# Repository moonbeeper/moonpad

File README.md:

# moonpad

> [!NOTE]
> This project is still not in a finished state. It does not work.
> This project comes from [Highway To Undercity](https://highway.hackclub.com/projects/moonbeeper/moonpad)

It's a modular macropad. Simple as that. You have an oled screen in the macropad and 2 modules that can be daisy chained and hot swapped. These two modules are the knobs and sliders module as I didn't want to overcomplicate my first project.

The primary reason for making this project was to just learn how to make PCBs and use microcontrollers like the RP2040 and ATTINY. It was a great adventure and I think I learned a lot. I mean, there's sure a lot of room for improvement but I'm happy with the result.

## Images

> Macropad

> Knobs Module

> Sliders Module

> Macropad PCB

> Knobs Module PCB

> Sliders Module PCB

## BOM

> **NOTE:** This is a copy of the BOM.csv file. The shipping cost might be actually higher than the price listed here.

| Item | Quantity | LCSC Part Number | Cost EUR | Cost USD | Link |
|---|---|---|---|---|---|
| 1uF Ceramic Cap | 34 | C116352 | 0,49 € | $0,56 | <https://lcsc.com/product-detail/Multilayer-Ceramic-Capacitors-MLCC-SMD-SMT_Samsung-Electro-Mechanics-CL21B105KAFNNNE_C116352.html> |
| 4.7k Ohm Resistor | 16 | C60816 | 0,20 € | $0,22 | <https://lcsc.com/product-detail/Chip-Resistor-Surface-Mount_YAGEO-RC0805FR-074K7L_C60816.html> |
| 10k Ohm Resistor | 8 | C17414 | 0,16 € | $0,18 | <https://lcsc.com/product-detail/Chip-Resistor-Surface-Mount_UNI-ROYAL-Uniroyal-Elec-0805W8F1002T5E_C17414.html> |
| 1N4148 Diode | 19 | C68883 | 0,55 € | $0,63 | <https://lcsc.com/product-detail/Switching-Diodes_Vishay-Intertech-LL4148-GS08_C68883.html> |
| TCA9546APWR | 1 | C201653 | 0,63 € | $0,73 | <https://lcsc.com/product-detail/Signal-Switches-Multiplexers-Decoders_TI-TCA9546APWR_C201653.html> |
| Cherry MX Red Switch | 8 | --- | 5,72 € | $6,68 | <https://es.aliexpress.com/item/1005006255961111.html> |
| XIAO RP2040 | 1 | --- | 6,25 € | $7,30 | <https://es.aliexpress.com/item/1005004459618789.html> |
| Oled Display 128x32 | 1 | --- | 1,97 € | $2,30 | <https://es.aliexpress.com/item/1005008640132638.html> |
| 5 pin magentic connector | 11 | --- | 3,13 € | $3,66 | <https://es.aliexpress.com/item/1005006531774076.html> |
| TS5A23166DCUR | 8 | C49148 | 3,85 € | $4,42 | <https://lcsc.com/product-detail/Analog-Switches-Multiplexers_Texas-Instruments-TS5A23166DCUR_C49148.html> |
| ATTINY1616-SNR | 2 | C609652 | 2,69 € | $3,09 | <https://lcsc.com/product-detail/Microcontrollers-MCU-MPU-SOC_Microchip-Tech-ATTINY1616-SNR_C609652.html> |
| TMUX4052PWR (Q1) | 2 | C20345958 | 0,59 € | $0,68 | <https://lcsc.com/product-detail/Analog-Switches-Multiplexers_TI-TMUX4052PWRQ1_C20345958.html> |
| ATTINY414-SSF | 2 | C1338163 | 2,73 € | $3,13 | <https://lcsc.com/product-detail/Microcontrollers-MCU-MPU-SOC_Microchip-Tech-ATTINY414-SSF_C1338163.html> |
| TCA4311ADGKR | 2 | C130025 | 1,81 € | $2,08 | <https://lcsc.com/product-detail/Signal-Buffers-Repeaters-Splitters_TI-TCA4311ADGKR_C130025.html> |
| Vertical SPDT Switch | 2 | C3008584 | 0,39 € | $0,44 | <https://lcsc.com/product-detail/Slide-Switches_SHOU-HAN-MSS12C02LS-HB2-0_C3008584.html> |
| ALPSALPINE RS45111A900F Potentiometer | 2 | C470640 | 2,81 € | $3,24 | <https://lcsc.com/product-detail/Potentiometers-Variable-Resistors_ALPSALPINE-RS45111A900F_C470640.html> |
| PMOSFET | 2 | C15127 | 0,56 € | $0,64 | <https://lcsc.com/product-detail/MOSFETs_Alpha-Omega-Semicon-AO3401A_C15127.html> |
| Header Pins | 2 | --- | 0,99 € | $1,16 | <https://es.aliexpress.com/item/4000873858801.html> |
| Encoder ALPSALPINE EC11E18244AU | 3 | C202365 | 5,13 € | $5,89 | <https://lcsc.com/product-detail/Rotary-Encoders_ALPSALPINE-EC11E18244AU_C202365.html> |
| JLCPCB Macropad PCB | 5 | --- | 3,32 € | $4,00 | --- |
| JLCPCB Slider PCB | 5 | --- | 5,98 € | $7,00 | --- |
| JLCPCB Knobs PCB | 5 | --- | 5,98 € | $7,00 | --- |
| M2 Heat Inserts OD3.5 Length 4mm | 12 | --- | 2,14 € | $2,50 | <https://es.aliexpress.com/item/1005003582355741.html> |
| M2 Allen Bolts 14mm Stainless Steel | 4 | --- | 2,03 € | $2,37 | <https://es.aliexpress.com/item/32810872544.html> |
| M2 Allen Bolts 10mm Stainless Steel | 8 | --- | 1,77 € | $2,07 | <https://es.aliexpress.com/item/32810872544.html> |
| Cherry MX Plate mounted Stabilizer | 1 | --- | 5,44 € | $6,35 | <https://es.aliexpress.com/item/1005001831944910.html> |
| 1U DSA Yellow Keycaps | 7 | --- | 3,39 € | $3,96 | <https://es.aliexpress.com/item/1005002906017844.html> |
| 2U DSA Gray Keycaps | 1 | --- | 6,92 € | $8,08 | <https://es.aliexpress.com/item/4001241957677.html> |
| UPDI Friend (Programmer) | 1 | --- | 7,77 € | $9,08 | <https://es.aliexpress.com/item/1005007180681621.html> |
| Flux | 1 | --- | 3,63 € | $4,24 | <https://es.aliexpress.com/item/1005006982454206.html> |
| ~Shipping | --- | --- | 15,07 € | $17,60 | --- |
| TOTAL | --- | --- | 104,09 € | $121,28 | --- |
|  |  |  |  |  |  |

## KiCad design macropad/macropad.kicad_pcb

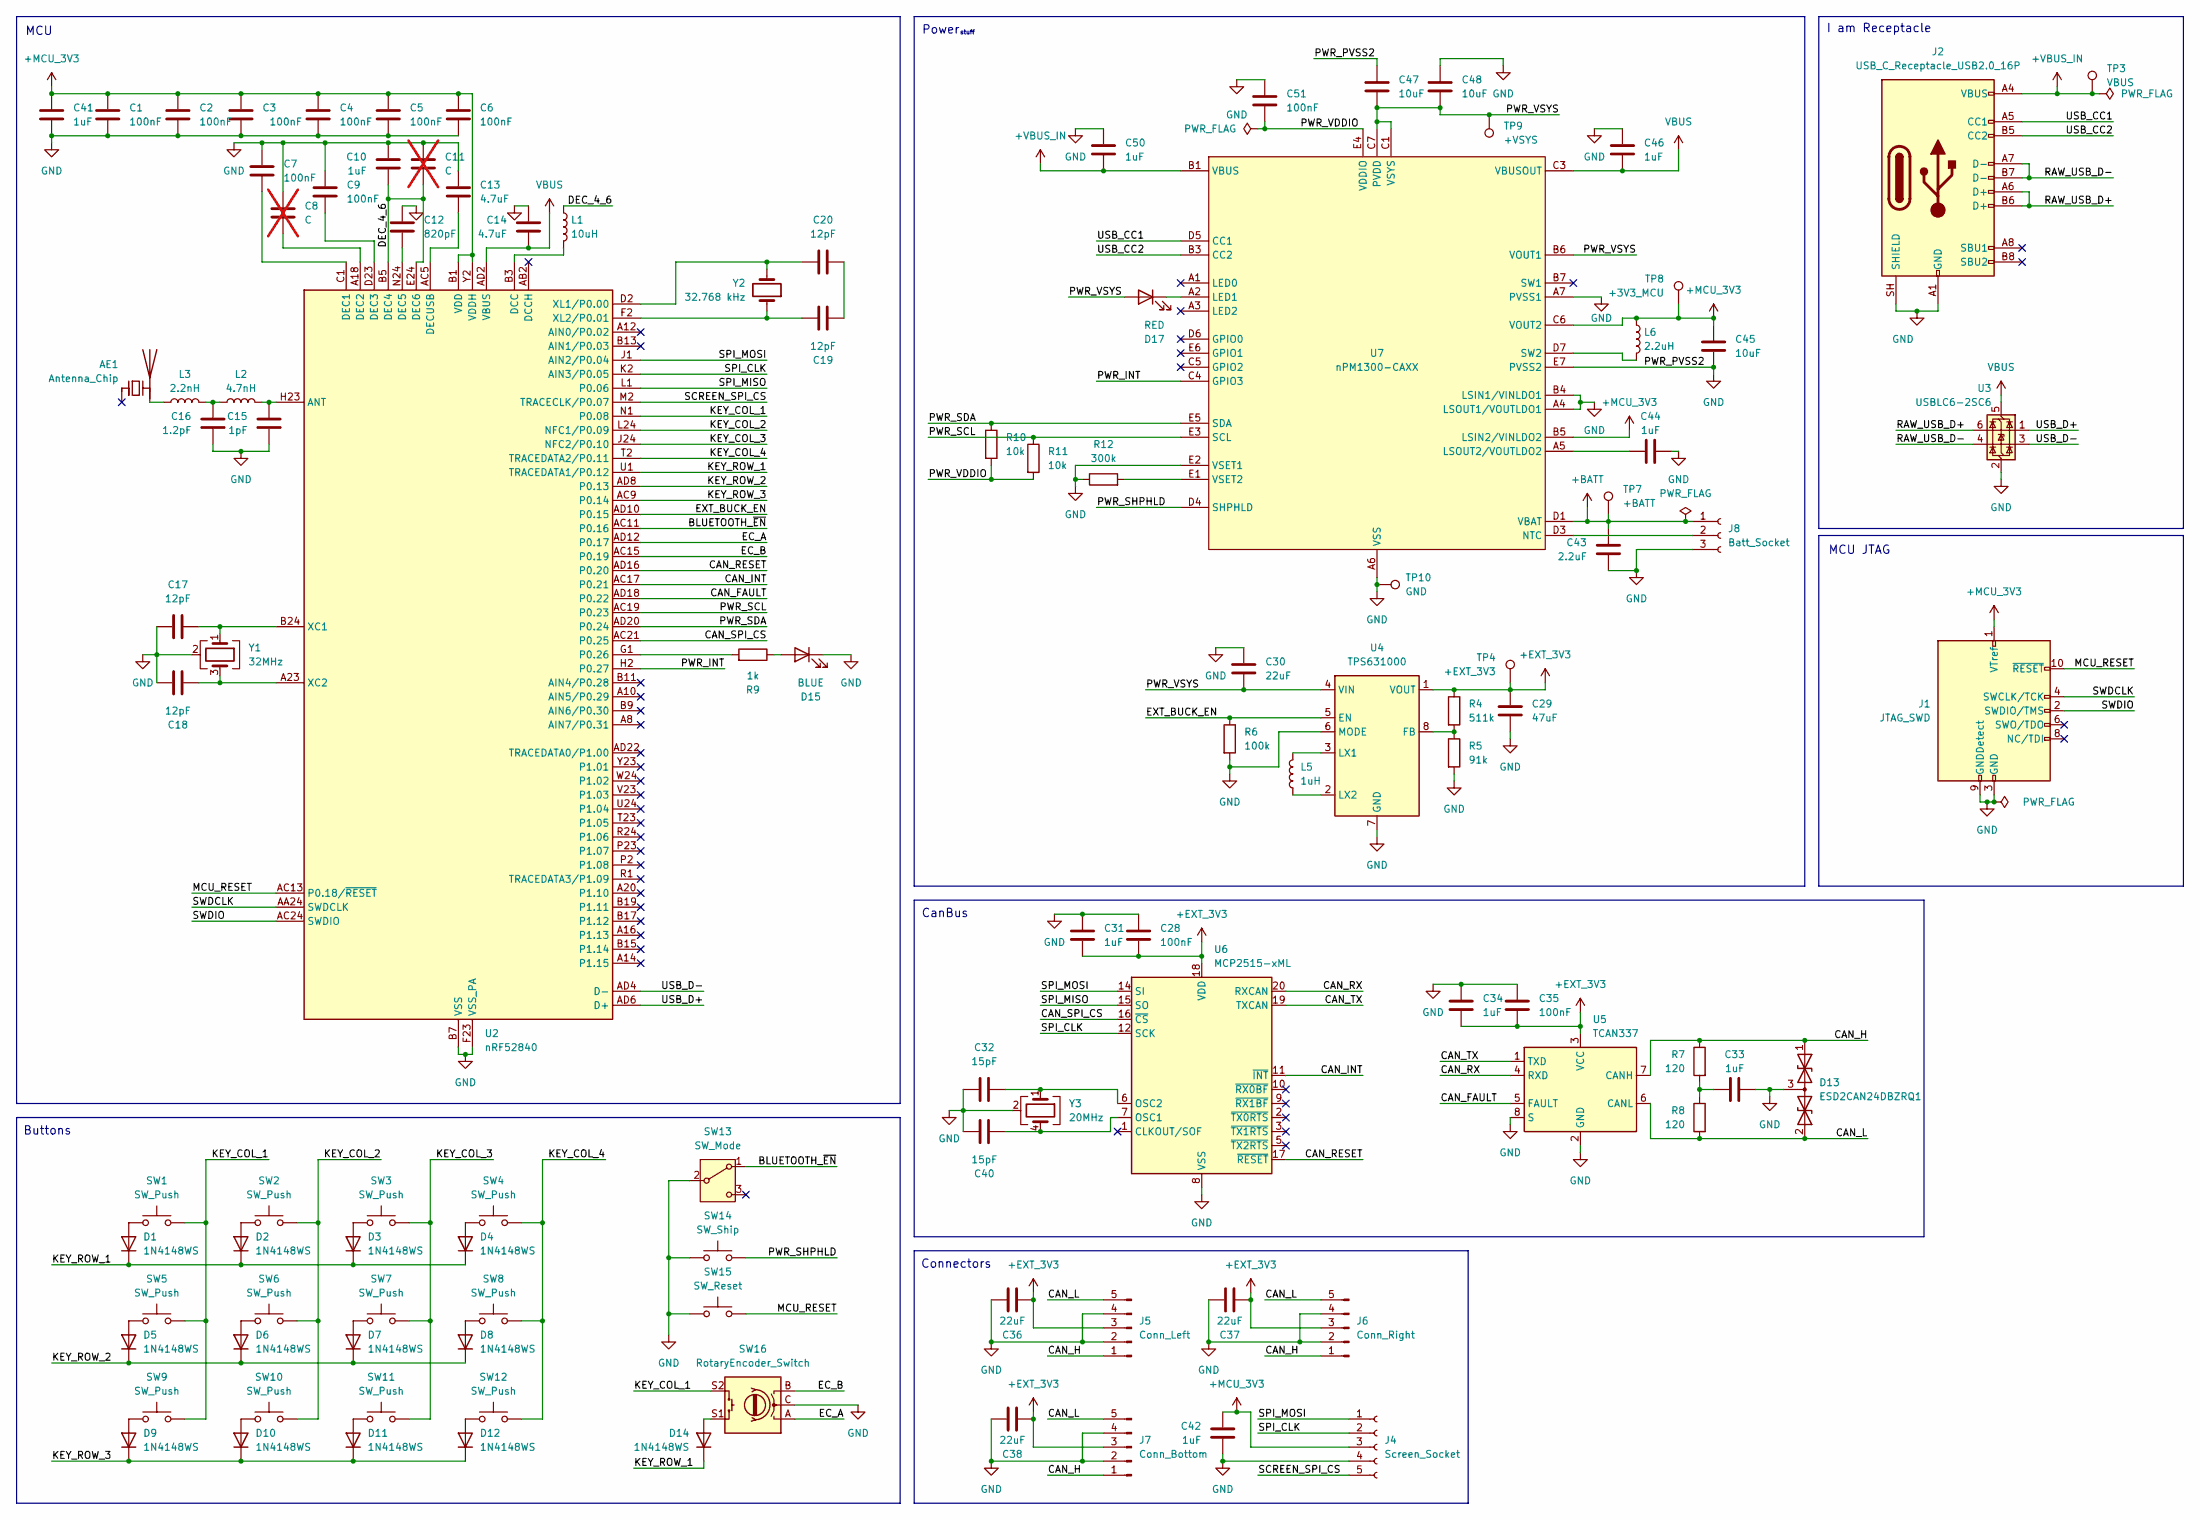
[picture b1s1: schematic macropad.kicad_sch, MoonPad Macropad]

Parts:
AE1: Antenna_Chip; D_1206_3216Metric; MPN ANT3216LL00R2400A; LCSC C293767
C1, C2, C3, C4, C5, C6, C7, C9, C28, C35, C51: 100nF; C_0603_1608Metric; MPN CC0603KRX7R9BB104; LCSC C14663
C8, C11: C; not fitted
C10, C31, C33, C34, C41, C42, C44, C46, C50: 1uF; C_0603_1608Metric; MPN CL10B105KB8NQNC; LCSC C5199872
C12: 820pF; C_0603_1608Metric; MPN CC0603JRNPO9BN821; LCSC C107057
C13, C14: 4.7uF; C_0603_1608Metric; MPN GRM188Z71C475KE21D; LCSC C389010
C15: 1pF; C_0402_1005Metric; MPN CC0402BRNPO9BN1R0; LCSC C309455
C16: 1.2pF; C_0402_1005Metric; MPN CC0402BRNPO9BN1R2; LCSC C327292
C17, C18, C19, C20: 12pF; C_0603_1608Metric; MPN CC0603GRNPO9BN120; LCSC C519450
C29: 47uF; C_0805_2012Metric; MPN GRM21BR61A476ME15L; LCSC C124129
C30, C36, C37, C38: 22uF; C_0805_2012Metric; MPN CL21A226MPQNNNE; LCSC C29277
C32, C40: 15pF; C_0603_1608Metric; MPN CC0603GRNPO9BN150; LCSC C519451
C43: 2.2uF; C_0603_1608Metric; MPN CL10A225KB8NNNC; LCSC C913904
C45, C47, C48: 10uF; C_0603_1608Metric; MPN GRM188R61E106KA73D; LCSC C344022
D1, D2, D3, D4, D5, D6, D7, D8, D9, D10, D11, D12, D14: 1N4148WS; D_SOD-323; MPN 1N4148WS; LCSC C917117
D13: ESD2CAN24DBZRQ1; SOT-23-3; MPN ESD2CAN24DBZRQ1
D15: BLUE; LED_0603_1608Metric; MPN GL0603UB01; LCSC C51933294
D17: RED; LED_0603_1608Metric; MPN GL0603UR01; LCSC C51933292
J1: JTAG_SWD; PinHeader_2x05_P1.27mm_Vertical
J2: USB_C_Receptacle_USB2.0_16P; USB_C_Receptacle_G-Switch_GT-USB-7010ASV; MPN GT-USB-7010ASV; LCSC C2988369
J4: Screen_Socket; PinHeader_1x05_P2.00mm_Vertical
J5: Conn_Left; PinHeader_1x05_P2.00mm_Vertical
J6: Conn_Right; PinHeader_1x05_P2.00mm_Vertical
J7: Conn_Bottom; PinHeader_1x05_P2.00mm_Vertical
J8: Batt_Socket; PinHeader_1x05_P2.00mm_Vertical
L1: 10uH; L_0603_1608Metric; MPN MLZ1608N100LT000; LCSC C194437
L2: 4.7nH; L_0402_1005Metric; MPN LQG15HS4N7S02D; LCSC C86065
L3: 2.2nH; L_0402_1005Metric; MPN LQG15HS2N2S02D; LCSC C86061
L5: 1uH; L_1008_2520Metric; MPN DFE252012P-1R0M=P2; LCSC C882955
L6: 2.2uH; L_0805_2012Metric; MPN DFE201210U-2R2M=P2; LCSC C2049745
R4: 511k; R_0603_1608Metric; MPN FRC0603F5113TS; LCSC C2930114
R5: 91k; R_0603_1608Metric; MPN FRC0603F9102TS; LCSC C2907077
R6: 100k; R_0603_1608Metric; MPN FRC0603F1003TS; LCSC C2906980
R7, R8: 120; R_0603_1608Metric; MPN FRC0603F1200TS; LCSC C2906988
R9: 1k; R_0603_1608Metric; MPN FRC0603F1001TS; LCSC C2907002
R10, R11: 10k; R_0603_1608Metric; MPN FRC0603J103 TS; LCSC C2930027
R12: 300k; R_0603_1608Metric; MPN FRC0603F3003TS; LCSC C2930091
SW1, SW2, SW3, SW4, SW5, SW6, SW7, SW8, SW9, SW10, SW11, SW12: SW_Push; SW_Hotswap_Kailh_Choc_V1V2_1.00u
SW13: SW_Mode; SW-SMD_MK-12C02-G020; MPN MK-12C02-G020; LCSC C963206
SW14: SW_Ship; KEY-SMD_SKRTLAE010; MPN SKRTLAE010; LCSC C110293
SW15: SW_Reset; KEY-SMD_B3U-1000PM; MPN B3U-1000P; LCSC C231329
SW16: RotaryEncoder_Switch; RotaryEncoder_Alps_EC11E-Switch_Vertical_H20mm; MPN EC11E09244BS; LCSC C470742
TP3: VBUS; TestPoint_Pad_D1.5mm
TP4: +EXT_3V3; TestPoint_Pad_D1.5mm
TP7: +BATT; TestPoint_Pad_D1.5mm
TP8: +3V3_MCU; TestPoint_Pad_D1.5mm
TP9: +VSYS; TestPoint_Pad_D1.5mm
TP10: GND; TestPoint_Pad_D1.5mm
U2: nRF52840; Nordic_AQFN-73-1EP_7x7mm_P0.5mm; MPN NRF52840-QIAA-F-R7
U3: USBLC6-2SC6; SOT-23-6; MPN USBLC6-2SC6; LCSC C2827654
U4: TPS631000; SOT-583-8; MPN TPS631000DRLR; LCSC C5219190
U5: TCAN337; SOIC-8_3.9x4.9mm_P1.27mm; MPN TCAN337DR; LCSC C2860648
U6: MCP2515-xML; QFN-20-1EP_4x4mm_P0.5mm_EP2.7x2.7mm; MPN MCP2515T-I/ML; LCSC C96140
U7: nPM1300-CAXX; BGA-35_7x5_3.077x2.3775mm; MPN NPM1300-CAAA-R
Y1: 32MHz; Crystal_SMD_2016-4Pin_2.0x1.6mm; MPN TX201632M4BBCE2T; LCSC C5339095
Y2: 32.768 kHz; Crystal_SMD_2012-2Pin_2.0x1.2mm; MPN SC-20S,32.768kHz,20PPM,9pF; LCSC C97603
Y3: 20MHz; Crystal_SMD_3225-4Pin_3.2x2.5mm; MPN 2.1.3.1600011; LCSC C42420972

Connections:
+BATT: C43.1, J8.1, TP7.1 (1_1), U7.D1 (VBAT), U7.D2 (VBAT)
+EXT_3V3: C28.2, C29.1, C31.2, C34.2, C35.2, C36.1, C37.1, C38.1, J5.3, J6.3, J7.3, R4.1, TP4.1 (1_1), U4.1 (VOUT), U5.3 (VCC), U6.18 (VDD)
+MCU_3V3: C1.1, C2.1, C3.1, C4.1, C5.1, C6.1, C41.1, C42.1, C45.1, J1.1 (VTref), J4.3, L6.1, TP8.1 (1_1), U2.A22 (VDD), U2.AD14 (VDD), U2.AD23 (VDD), U2.B1 (VDD), U2.W1 (VDD), U2.Y2 (VDDH), U7.B5 (LSIN2/VINLDO2), U7.C6 (VOUT2)
+VBUS_IN: C50.2, J2.A4 (VBUS), J2.A9 (VBUS), J2.B4 (VBUS), J2.B9 (VBUS), TP3.1 (1_1), U7.B1 (VBUS), U7.B2 (VBUS)
/BLUETOOTH_~EN: SW13.1 (A), U2.AC11 (P0.16)
/CAN_FAULT: U2.AD18 (P0.22), U5.5 (FAULT)
/CAN_H: D13.1 (A1), J5.1, J6.1, J7.1, R7.1, U5.7 (CANH)
/CAN_INT: U2.AC17 (P0.21), U6.11 (~INT)
/CAN_L: D13.2 (A2), J5.5, J6.5, J7.5, R8.2, U5.6 (CANL)
/CAN_RESET: U2.AD16 (P0.20), U6.17 (~RESET)
/CAN_RX: U5.4 (RXD), U6.20 (RXCAN)
/CAN_SPI_CS: U2.AC21 (P0.25), U6.16 (~CS)
/CAN_TX: U5.1 (TXD), U6.19 (TXCAN)
/DEC_4_6: C10.2, C11.2, L1.1, U2.B5 (DEC4), U2.E24 (DEC6)
/EC_A: SW16.A, U2.AD12 (P0.17)
/EC_B: SW16.B, U2.AC15 (P0.19)
/EXT_BUCK_EN: R6.1, U2.AD10 (P0.15), U4.5 (EN)
/KEY_COL_1: SW1.2, SW5.2, SW9.2, SW16.S2, U2.N1 (P0.08)
/KEY_COL_2: SW2.2, SW6.2, SW10.2, U2.L24 (NFC1/P0.09)
/KEY_COL_3: SW3.2, SW7.2, SW11.2, U2.J24 (NFC2/P0.10)
/KEY_COL_4: SW4.2, SW8.2, SW12.2, U2.T2 (TRACEDATA2/P0.11)
/KEY_ROW_1: D1.1 (K), D2.1 (K), D3.1 (K), D4.1 (K), D14.1 (K), U2.U1 (TRACEDATA1/P0.12)
/KEY_ROW_2: D5.1 (K), D6.1 (K), D7.1 (K), D8.1 (K), U2.AD8 (P0.13)
/KEY_ROW_3: D9.1 (K), D10.1 (K), D11.1 (K), D12.1 (K), U2.AC9 (P0.14)
/MCU_RESET: J1.10 (~RESET), SW15.2, U2.AC13 (P0.18/~RESET)
/PWR_INT: U2.H2 (P0.27), U7.C4 (GPIO3)
/PWR_SCL: R11.1, U2.AC19 (P0.23), U7.E3 (SCL)
/PWR_SDA: R10.1, U2.AD20 (P0.24), U7.E5 (SDA)
/PWR_SHPHLD: SW14.2, U7.D4 (SHPHLD)
/PWR_VDDIO: C51.2, R10.2, R11.2, U7.E4 (VDDIO)
/PWR_VSYS: C30.2, C47.2, C48.2, D17.2 (A), TP9.1 (1_1), U4.4 (VIN), U7.B6 (VOUT1), U7.C1 (VSYS), U7.C2 (VSYS), U7.C7 (PVDD)
/RAW_USB_D+: J2.A6 (D+), J2.B6 (D+), U3.6 (I/O1)
/RAW_USB_D-: J2.A7 (D-), J2.B7 (D-), U3.4 (I/O2)
/SCREEN_SPI_CS: J4.5, U2.M2 (TRACECLK/P0.07)
/SPI_CLK: J4.2, U2.K2 (AIN3/P0.05), U6.12 (SCK)
/SPI_MISO: U2.L1 (P0.06), U6.15 (SO)
/SPI_MOSI: J4.1, U2.J1 (AIN2/P0.04), U6.14 (SI)
/SWDCLK: J1.4 (SWCLK/TCK), U2.AA24 (SWDCLK)
/SWDIO: J1.2 (SWDIO/TMS), U2.AC24 (SWDIO)
/USB_CC1: J2.A5 (CC1), U7.D5 (CC1)
/USB_CC2: J2.B5 (CC2), U7.B3 (CC2)
/USB_D+: U2.AD6 (D+), U3.1 (I/O1)
/USB_D-: U2.AD4 (D-), U3.3 (I/O2)
GND: C1.2, C2.2, C3.2, C4.2, C5.2, C6.2, C7.1, C8.1, C9.1, C10.1, C11.1, C12.1, C13.1, C14.1, C15.2, C16.2, C17.2, C18.2, C28.1, C29.2, C30.1, C31.1, C32.1, C33.2, C34.1, C35.1, C36.2, C37.2, C38.2, C40.1, C41.2, C42.2, C43.2, C44.2, C45.2, C46.1, C47.1, C48.1, C50.1, C51.1, D13.3 (common), D15.1 (K), J1.3 (GND), J1.5 (GND), J1.9 (GNDDetect), J2.A1 (GND), J2.A12 (GND), J2.B1 (GND), J2.B12 (GND), J2.SH (SHIELD), J4.4, J5.2, J5.4, J6.2, J6.4, J7.2, J7.4, J8.3, R5.2, R6.2, R12.1, SW13.2 (B), SW14.1, SW15.1, SW16.C, TP10.1 (1_1), U2.B7 (VSS), U2.EP (VSS), U2.F23 (VSS_PA), U3.2 (GND), U4.6 (MODE), U4.7 (GND), U5.2 (GND), U5.8 (S), U6.8 (VSS), U6.21 (EP), U7.A4 (LSOUT1/VOUTLDO1), U7.A6 (VSS), U7.A7 (PVSS1), U7.B4 (LSIN1/VINLDO1), U7.E2 (VSET1), U7.E7 (PVSS2), Y1.2 (G), Y1.4 (G), Y3.2 (G), Y3.3 (G)
unnamed: AE1.2 (PCB_Trace_2), L3.1
unnamed: C16.1, L2.1, L3.2
unnamed: C19.2, C20.2
unnamed: C33.1, R7.2, R8.1
unnamed: D1.2 (A), SW1.1
unnamed: D2.2 (A), SW2.1
unnamed: D3.2 (A), SW3.1
unnamed: D4.2 (A), SW4.1
unnamed: D5.2 (A), SW5.1
unnamed: D6.2 (A), SW6.1
unnamed: D7.2 (A), SW7.1
unnamed: D8.2 (A), SW8.1
unnamed: D9.2 (A), SW9.1
unnamed: D10.2 (A), SW10.1
unnamed: D11.2 (A), SW11.1
unnamed: D12.2 (A), SW12.1
unnamed: D14.2 (A), SW16.S1
unnamed: D15.2 (A), R9.1
unnamed: D17.1 (K), U7.A2 (LED1)
unnamed: J8.2, U7.D3 (NTC)
unnamed: C15.1, L2.2, U2.H23 (ANT)
unnamed: L1.2, U2.B3 (DCC)
unnamed: C7.2, U2.C1 (DEC1)
unnamed: C8.2, U2.A18 (DEC2)
unnamed: C9.2, U2.D23 (DEC3)
unnamed: C12.2, U2.N24 (DEC5)
unnamed: C13.2, U2.AC5 (DECUSB)
unnamed: R9.2, U2.G1 (P0.26)
unnamed: C17.1, U2.B24 (XC1), Y1.1
unnamed: C18.1, U2.A23 (XC2), Y1.3
unnamed: C20.1, U2.D2 (XL1/P0.00), Y2.2
unnamed: C19.1, U2.F2 (XL2/P0.01), Y2.1
unnamed: R4.2, R5.1, U4.8 (FB)
unnamed: L5.2, U4.3 (LX1)
unnamed: L5.1, U4.2 (LX2)
unnamed: C40.2, U6.7 (OSC1), Y3.4
unnamed: C32.2, U6.6 (OSC2), Y3.1
unnamed: C44.1, U7.A5 (LSOUT2/VOUTLDO2)
unnamed: L6.2, U7.D7 (SW2)
unnamed: R12.2, U7.E1 (VSET2)
VBUS: C14.2, C46.2, U2.AD2 (VBUS), U3.5 (VBUS), U7.C3 (VBUSOUT)

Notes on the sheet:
Power
MCU
Buttons
stuff
I am Receptacle
CanBus
Connectors
MCU JTAG

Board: 2 copper layers, 109 parts (0 on the bottom side), 84 nets, no tracks yet.

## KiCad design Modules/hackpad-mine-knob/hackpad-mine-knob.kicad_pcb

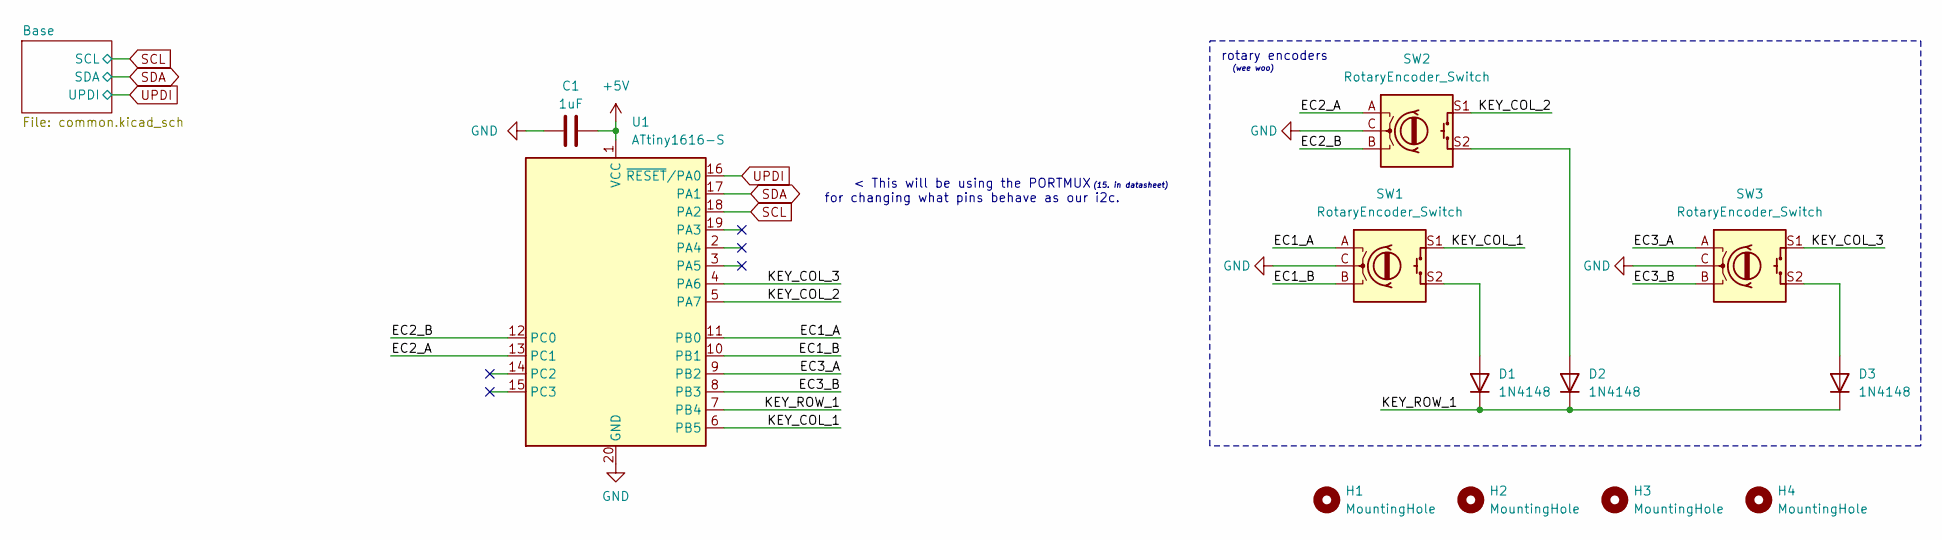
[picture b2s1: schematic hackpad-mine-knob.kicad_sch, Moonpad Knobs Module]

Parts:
C1: 1uF; C_0805_2012Metric_Pad1.18x1.45mm_HandSolder; LCSC C116352
D1, D2, D3: 1N4148; D_MiniMELF_Handsoldering; LCSC C68883
H1, H2, H3, H4: MountingHole; MountingHole_2.2mm_M2
SW1, SW2, SW3: RotaryEncoder_Switch; RotaryEncoder_Alps_EC11E-Switch_Vertical_H20mm_CircularMoun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; LCSC C202365
U1: ATtiny1616-S; SOIC-20W_7.5x12.8mm_P1.27mm; LCSC C609652

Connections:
+5V: C1.2, U1.1 (VCC); also elsewhere on the board
/EC1_A: SW1.A, U1.11 (PB0)
/EC1_B: SW1.B, U1.10 (PB1)
/EC2_A: SW2.A, U1.13 (PC1)
/EC2_B: SW2.B, U1.12 (PC0)
/EC3_A: SW3.A, U1.9 (PB2)
/EC3_B: SW3.B, U1.8 (PB3)
/KEY_COL_1: SW1.S1, U1.6 (PB5)
/KEY_COL_2: SW2.S1, U1.5 (PA7)
/KEY_COL_3: SW3.S1, U1.4 (PA6)
/KEY_ROW_1: D1.1 (K), D2.1 (K), D3.1 (K), U1.7 (PB4)
GND: C1.1, SW1.C, SW2.C, SW3.C, U1.20 (GND); also elsewhere on the board
unnamed: D1.2 (A), SW1.S2
unnamed: D2.2 (A), SW2.S2
unnamed: D3.2 (A), SW3.S2
SCL: U1.18 (PA2); also elsewhere on the board
SDA: U1.17 (PA1); also elsewhere on the board
UPDI: U1.16 (~RESET/PA0); also elsewhere on the board

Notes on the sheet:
(wee woo)
(15. in datasheet)
rotary encoders
< This will be using the PORTMUX for changing what pins behave as our i2c.

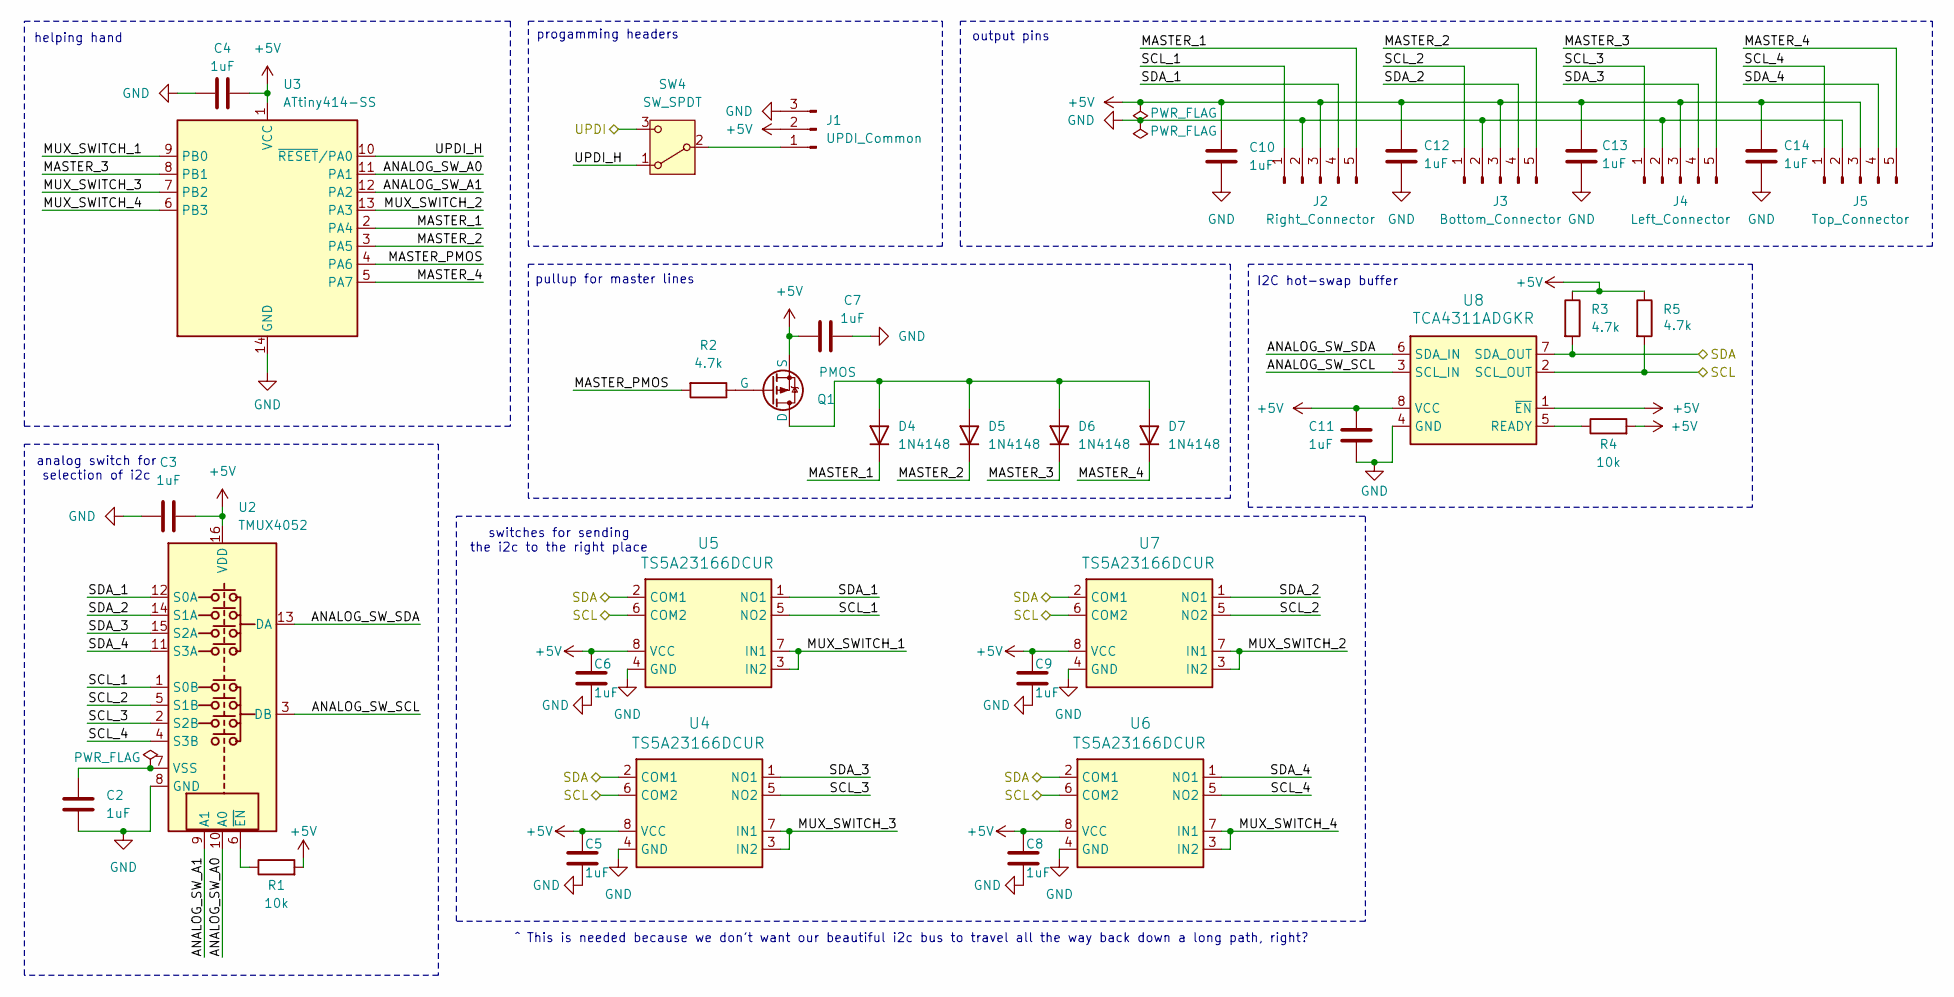
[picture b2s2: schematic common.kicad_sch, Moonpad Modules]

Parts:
C2, C3, C4, C5, C6, C7, C8, C9, C10, C11, C12, C13, C14: 1uF; C_0805_2012Metric_Pad1.18x1.45mm_HandSolder; LCSC C116352
D4, D5, D6, D7: 1N4148; D_MiniMELF_Handsoldering; LCSC C68883
J1: UPDI_Common; PinHeader_1x03_P2.54mm_Vertical
J2: Right_Connector; PinHeader_1x05_P2.54mm_Vertical
J3: Bottom_Connector; PinHeader_1x05_P2.54mm_Vertical
J4: Left_Connector; PinHeader_1x05_P2.54mm_Vertical
J5: Top_Connector; PinHeader_1x05_P2.54mm_Vertical
Q1: PMOS; SOT-23_Handsoldering; LCSC C15127
R1, R4: 10k; R_0805_2012Metric_Pad1.20x1.40mm_HandSolder; LCSC C17414
R2, R3, R5: 4.7k; R_0805_2012Metric_Pad1.20x1.40mm_HandSolder; LCSC C60816
SW4: SW_SPDT; SW-SMD_MSS12C02LS-HB2.0-1; LCSC C3008584
U2: TMUX4052; TSSOP-16_4.4x5mm_P0.65mm; LCSC C7362466
U3: ATtiny414-SS; SOIC-14_3.9x8.7mm_P1.27mm; LCSC C1338163
U4, U5, U6, U7: TS5A23166DCUR; VSSOP-8_2.3x2mm_P0.5mm; LCSC C49148
U8: TCA4311ADGKR; VSSOP-8_3x3mm_P0.65mm; LCSC C130025

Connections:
+5V: C3.2, C4.2, C5.2, C6.2, C7.2, C8.2, C9.2, C10.1, C11.1, C12.1, C13.1, C14.1, J1.2, J2.3, J3.3, J4.3, J5.3, Q1.3 (S), R1.2, R3.1, R4.2, R5.1, U2.16 (VDD), U3.1 (VCC), U4.8 (VCC), U5.8 (VCC), U6.8 (VCC), U7.8 (VCC), U8.1 (~EN), U8.8 (VCC); also elsewhere on the board
/Base/ANALOG_SW_A0: U2.10 (A0), U3.11 (PA1)
/Base/ANALOG_SW_A1: U2.9 (A1), U3.12 (PA2)
/Base/ANALOG_SW_SCL: U2.3 (DB), U8.3 (SCL_IN)
/Base/ANALOG_SW_SDA: U2.13 (DA), U8.6 (SDA_IN)
/Base/MASTER_1: D4.1 (K), J2.5, U3.2 (PA4)
/Base/MASTER_2: D5.1 (K), J3.5, U3.3 (PA5)
/Base/MASTER_3: D6.1 (K), J4.5, U3.8 (PB1)
/Base/MASTER_4: D7.1 (K), J5.5, U3.5 (PA7)
/Base/MASTER_PMOS: R2.2, U3.4 (PA6)
/Base/MUX_SWITCH_1: U3.9 (PB0), U5.3 (IN2), U5.7 (IN1)
/Base/MUX_SWITCH_2: U3.13 (PA3), U7.3 (IN2), U7.7 (IN1)
/Base/MUX_SWITCH_3: U3.7 (PB2), U4.3 (IN2), U4.7 (IN1)
/Base/MUX_SWITCH_4: U3.6 (PB3), U6.3 (IN2), U6.7 (IN1)
/Base/SCL_1: J2.1, U2.1 (S0B), U5.5 (NO2)
/Base/SCL_2: J3.1, U2.5 (S1B), U7.5 (NO2)
/Base/SCL_3: J4.1, U2.2 (S2B), U4.5 (NO2)
/Base/SCL_4: J5.1, U2.4 (S3B), U6.5 (NO2)
/Base/SDA_1: J2.4, U2.12 (S0A), U5.1 (NO1)
/Base/SDA_2: J3.4, U2.14 (S1A), U7.1 (NO1)
/Base/SDA_3: J4.4, U2.15 (S2A), U4.1 (NO1)
/Base/SDA_4: J5.4, U2.11 (S3A), U6.1 (NO1)
/Base/UPDI_H: SW4.1 (A), U3.10 (~RESET/PA0)
GND: C2.2, C3.1, C4.1, C5.1, C6.1, C7.1, C8.1, C9.1, C10.2, C11.2, C12.2, C13.2, C14.2, J1.3, J2.2, J3.2, J4.2, J5.2, U2.8 (GND), U3.14 (GND), U4.4 (GND), U5.4 (GND), U6.4 (GND), U7.4 (GND), U8.4 (GND); also elsewhere on the board
unnamed: D4.2 (A), D5.2 (A), D6.2 (A), D7.2 (A), Q1.1 (D)
unnamed: J1.1, SW4.2 (B)
unnamed: Q1.2 (G), R2.1
unnamed: C2.1, U2.7 (VSS)
unnamed: R1.1, U2.6 (~EN)
unnamed: R4.1, U8.5 (READY)
SCL: R5.2, U4.6 (COM2), U5.6 (COM2), U6.6 (COM2), U7.6 (COM2), U8.2 (SCL_OUT); also elsewhere on the board
SDA: R3.2, U4.2 (COM1), U5.2 (COM1), U6.2 (COM1), U7.2 (COM1), U8.7 (SDA_OUT); also elsewhere on the board
UPDI: SW4.3 (C); also elsewhere on the board

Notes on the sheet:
helping hand
progamming headers
I2C hot-swap buffer
pullup for master lines
output pins
switches for sending the i2c to the right place
^ This is needed because we don't want our beautiful i2c bus to travel all the way back down a long path, right?
analog switch for selection of i2c

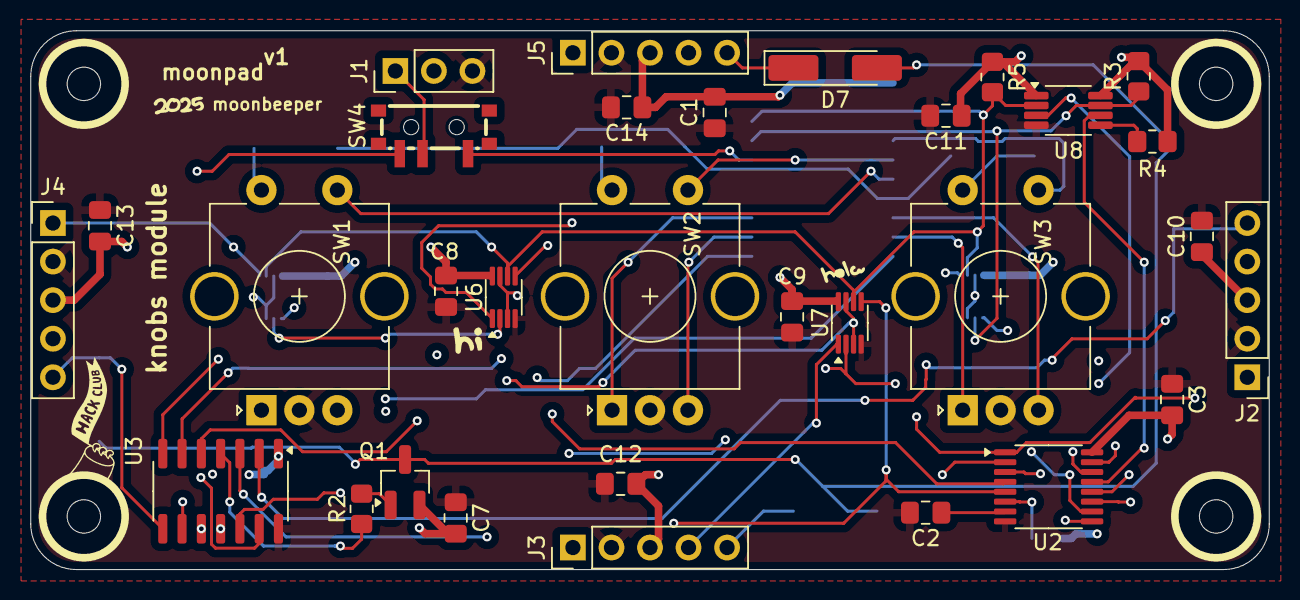
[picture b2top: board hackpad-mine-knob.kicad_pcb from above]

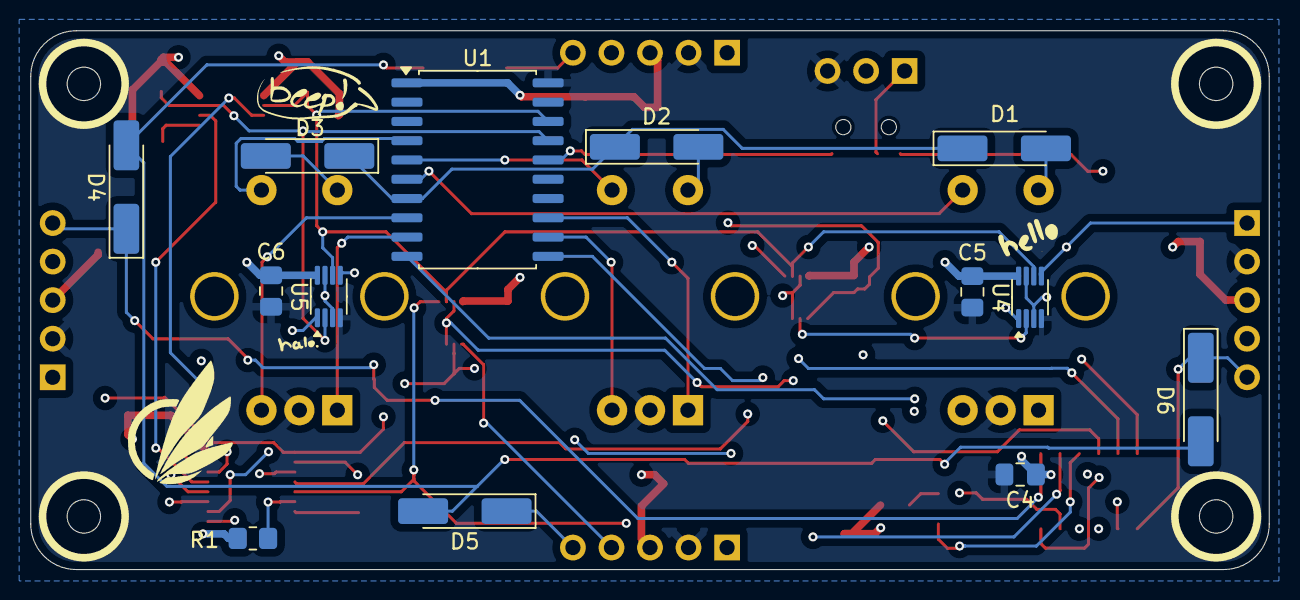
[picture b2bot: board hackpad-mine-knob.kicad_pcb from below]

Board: 4 copper layers, 81.6 x 35.5 mm, 48 parts (13 on the bottom side), 46 nets.

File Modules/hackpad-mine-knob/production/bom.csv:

Designator,Footprint,Quantity,Value,LCSC Part #
"C1, C10, C11, C12, C13, C14, C2, C3, C4, C5, C6, C7, C8, C9",0805,14,1uF,C116352
"D1, D2, D3, D4, D5, D6, D7",D_MiniMELF_Handsoldering,7,1N4148,C68883
J1,PinHeader_1x03_P2.54mm_Vertical,1,UPDI_Common,
J2,PinHeader_1x05_P2.54mm_Vertical,1,Right_Connector,
J3,PinHeader_1x05_P2.54mm_Vertical,1,Bottom_Connector,
J4,PinHeader_1x05_P2.54mm_Vertical,1,Left_Connector,
J5,PinHeader_1x05_P2.54mm_Vertical,1,Top_Connector,
Q1,SOT-23_Handsoldering,1,PMOS,C15127
"R1, R4",0805,2,10k,C17414
"R2, R3, R5",0805,3,4.7k,C60816
"SW1, SW2, SW3",RotaryEncoder_Alps_EC11E-Switch_Vertical_H20mm_CircularMountingHoles,3,RotaryEncoder_Switch,C202365
SW4,SW-SMD_MSS12C02LS-HB2.0-1,1,SW_SPDT,C3008584
U1,SOIC-20W_7.5x12.8mm_P1.27mm,1,ATtiny1616-S,C609652
U2,TSSOP-16_4.4x5mm_P0.65mm,1,TMUX4052,C7362466
U3,SOIC-14_3.9x8.7mm_P1.27mm,1,ATtiny414-SS,C1338163
"U4, U5, U6, U7",VSSOP-8_2.3x2mm_P0.5mm,4,TS5A23166DCUR,C49148
U8,VSSOP-8_3x3mm_P0.65mm,1,TCA4311ADGKR,C130025

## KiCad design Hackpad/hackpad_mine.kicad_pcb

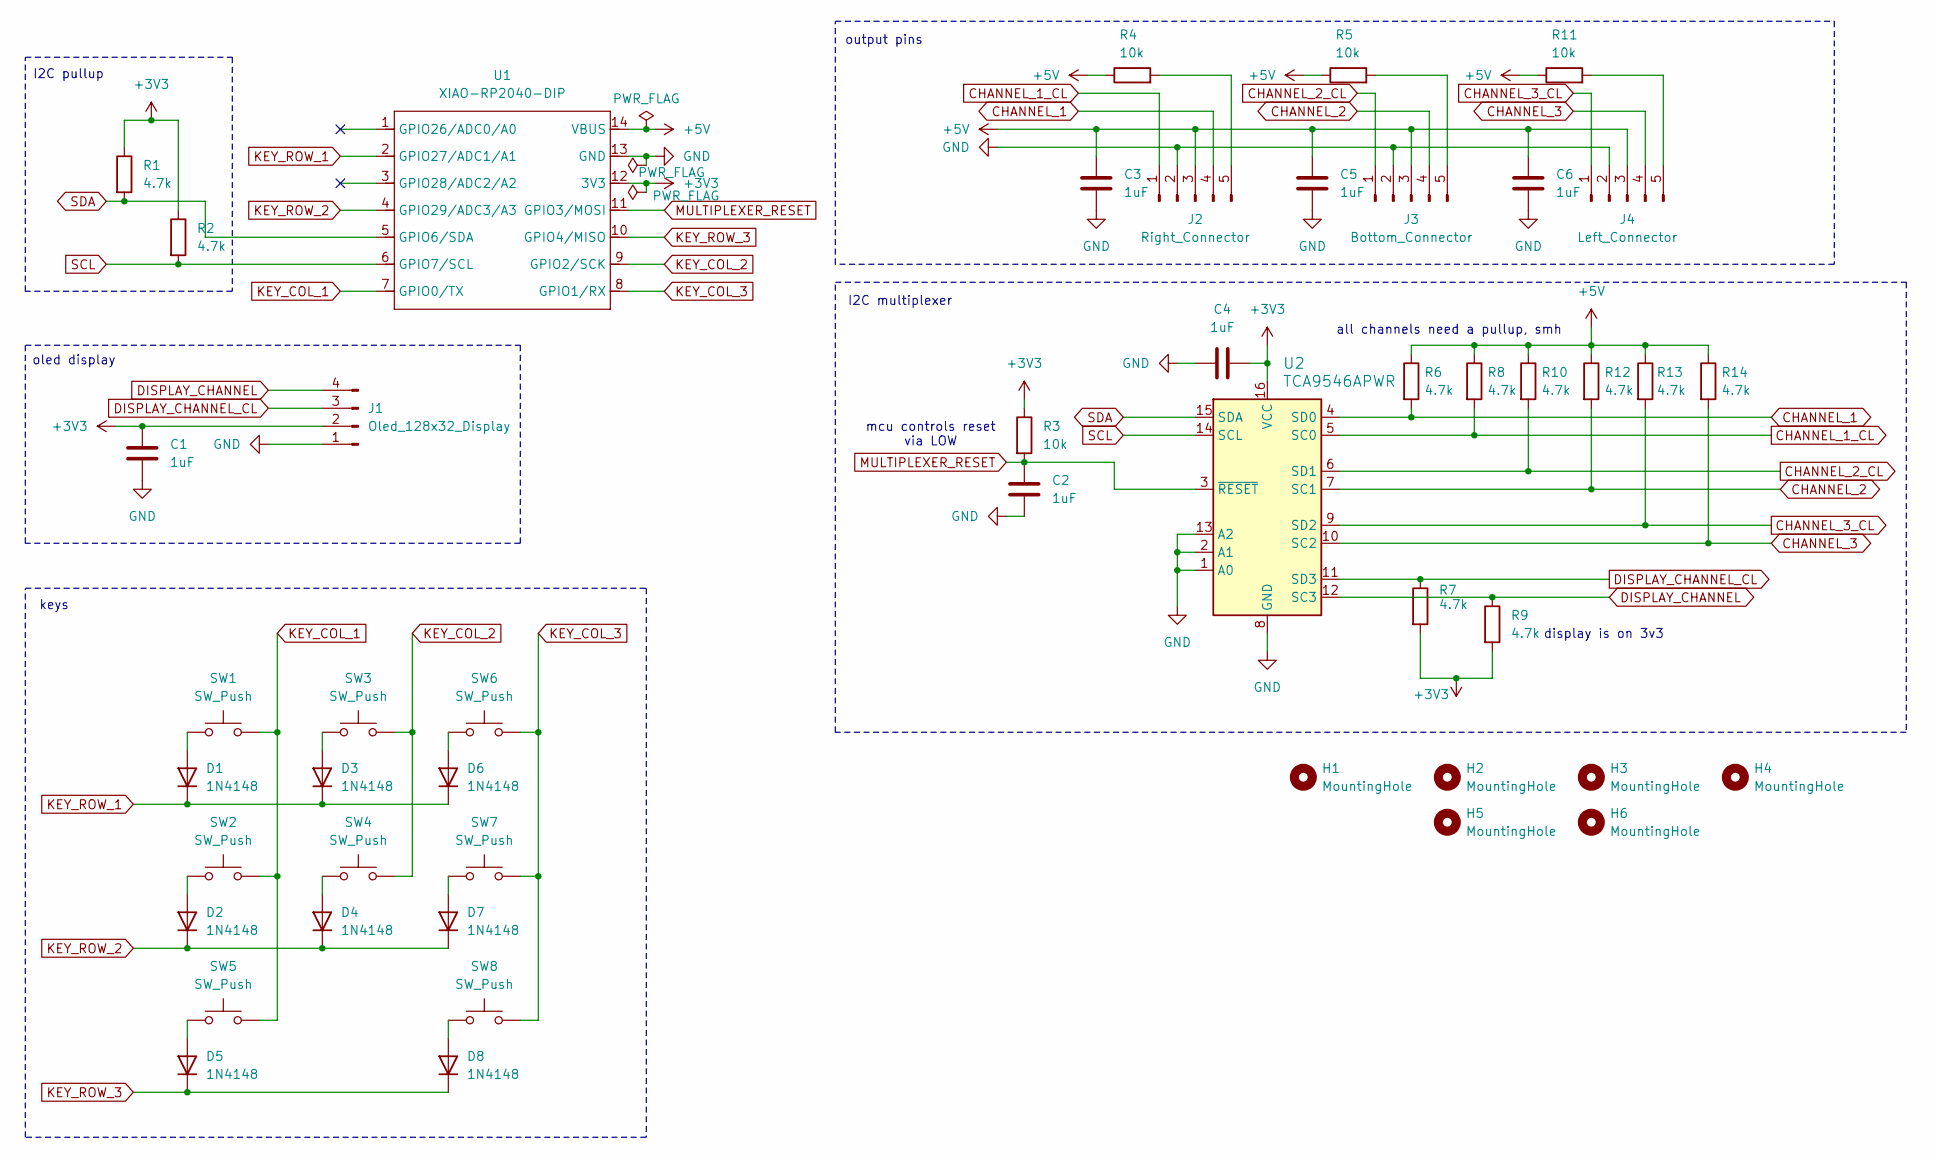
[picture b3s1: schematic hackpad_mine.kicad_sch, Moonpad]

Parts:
C1, C2, C3, C4, C5, C6: 1uF; C_0805_2012Metric_Pad1.18x1.45mm_HandSolder; LCSC C116352
D1, D2, D3, D4, D5, D6, D7, D8: 1N4148; D_MiniMELF_Handsoldering; LCSC C68883
H1, H2, H3, H4: MountingHole; MountingHole_2.2mm_M2
H5, H6: MountingHole; MountingHole_2.7mm_M2.5
J1: Oled_128x32_Display; PinHeader_1x04_P2.54mm_Vertical
J2: Right_Connector; PinHeader_1x05_P2.54mm_Vertical
J3: Bottom_Connector; PinHeader_1x05_P2.54mm_Vertical
J4: Left_Connector; PinHeader_1x05_P2.54mm_Vertical
R1, R2, R6, R7, R8, R9, R10, R12, R13, R14: 4.7k; R_0805_2012Metric_Pad1.20x1.40mm_HandSolder; LCSC C60816
R3, R4, R5, R11: 10k; R_0805_2012Metric_Pad1.20x1.40mm_HandSolder; LCSC C17414
SW1, SW2, SW3, SW4, SW5, SW6, SW7, SW8: SW_Push; SW_Cherry_MX_1.00u_PCB
U1: XIAO-RP2040-DIP
U2: TCA9546APWR; TSSOP-16_4.4x5mm_P0.65mm; LCSC C201653

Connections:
+3V3: C1.1, C4.2, J1.2, R1.1, R2.1, R3.1, R7.2, R9.2, U1.12 (3V3), U2.16 (VCC)
+5V: C3.1, C5.1, C6.1, J2.3, J3.3, J4.3, R4.1, R5.1, R6.1, R8.1, R10.1, R11.1, R12.1, R13.1, R14.1, U1.14 (VBUS)
CHANNEL_1: J2.4, R6.2, U2.4 (SD0)
CHANNEL_1_CL: J2.1, R8.2, U2.5 (SC0)
CHANNEL_2: J3.4, R12.2, U2.7 (SC1)
CHANNEL_2_CL: J3.1, R10.2, U2.6 (SD1)
CHANNEL_3: J4.4, R14.2, U2.10 (SC2)
CHANNEL_3_CL: J4.1, R13.2, U2.9 (SD2)
DISPLAY_CHANNEL: J1.4, R9.1, U2.12 (SC3)
DISPLAY_CHANNEL_CL: J1.3, R7.1, U2.11 (SD3)
GND: C1.2, C2.1, C3.2, C4.1, C5.2, C6.2, J1.1, J2.2, J3.2, J4.2, U1.13 (GND), U2.1 (A0), U2.2 (A1), U2.8 (GND), U2.13 (A2)
KEY_COL_1: SW1.2, SW2.2, SW5.2, U1.7 (GPIO0/TX)
KEY_COL_2: SW3.2, SW4.2, U1.9 (GPIO2/SCK)
KEY_COL_3: SW6.2, SW7.2, SW8.2, U1.8 (GPIO1/RX)
KEY_ROW_1: D1.1 (K), D3.1 (K), D6.1 (K), U1.2 (GPIO27/ADC1/A1)
KEY_ROW_2: D2.1 (K), D4.1 (K), D7.1 (K), U1.4 (GPIO29/ADC3/A3)
KEY_ROW_3: D5.1 (K), D8.1 (K), U1.10 (GPIO4/MISO)
MULTIPLEXER_RESET: C2.2, R3.2, U1.11 (GPIO3/MOSI), U2.3 (~RESET)
unnamed: D1.2 (A), SW1.1
unnamed: D2.2 (A), SW2.1
unnamed: D3.2 (A), SW3.1
unnamed: D4.2 (A), SW4.1
unnamed: D5.2 (A), SW5.1
unnamed: D6.2 (A), SW6.1
unnamed: D7.2 (A), SW7.1
unnamed: D8.2 (A), SW8.1
unnamed: J2.5, R4.2
unnamed: J3.5, R5.2
unnamed: J4.5, R11.2
SCL: R2.2, U1.6 (GPIO7/SCL), U2.14 (SCL)
SDA: R1.2, U1.5 (GPIO6/SDA), U2.15 (SDA)

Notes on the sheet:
mcu controls reset via LOW
I2C multiplexer
keys
output pins
oled display
display is on 3v3
I2C pullup
all channels need a pullup, smh
